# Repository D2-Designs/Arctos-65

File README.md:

# Arctos-65
Arctos 65 is a HHKB style 65% keyboard with a rotary encoder

Hello! This page is currently under construction. 

I plan to relase Version 1 of the project soon, which should fix all the issues with my innitial prototype, have more supported layouts, and be easier to manufacture.

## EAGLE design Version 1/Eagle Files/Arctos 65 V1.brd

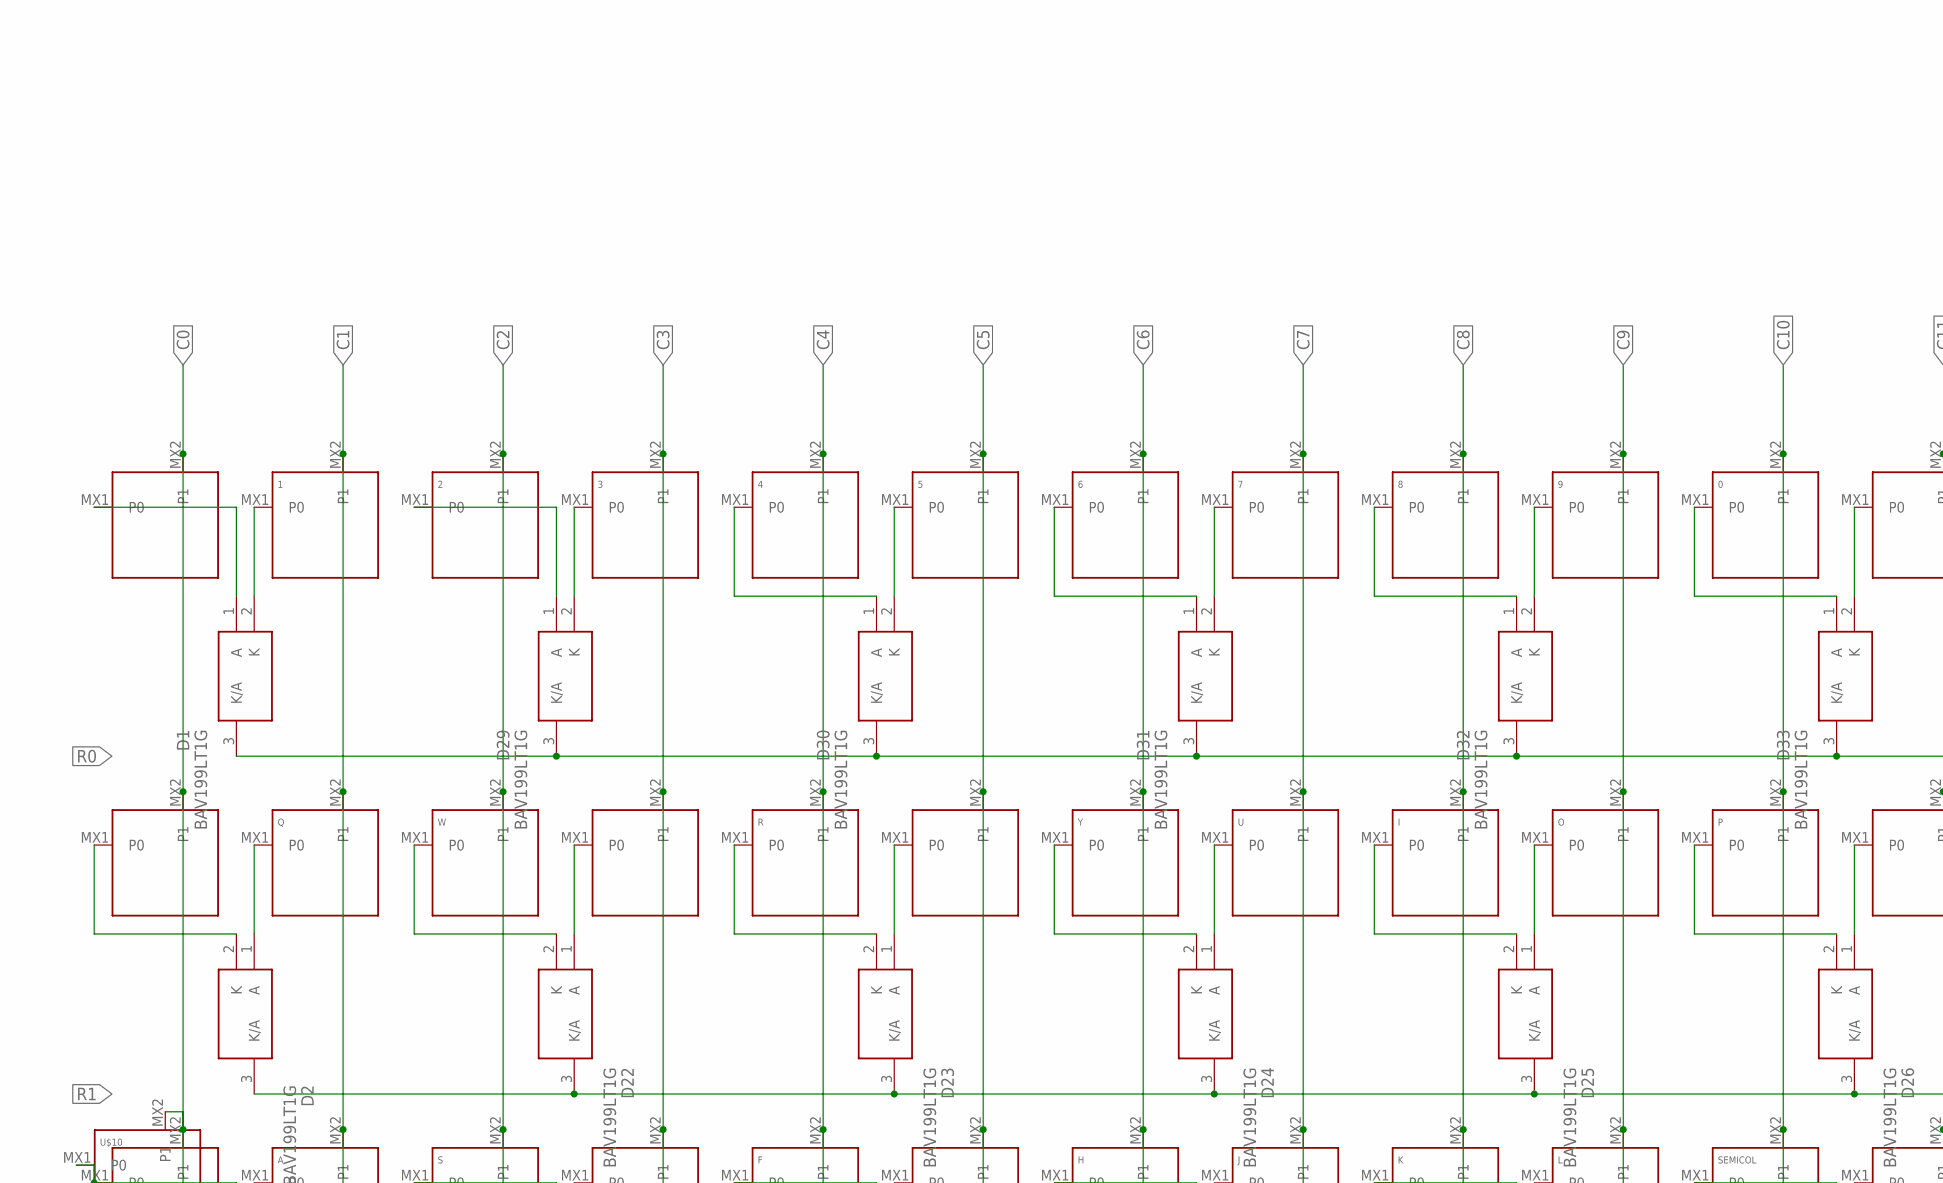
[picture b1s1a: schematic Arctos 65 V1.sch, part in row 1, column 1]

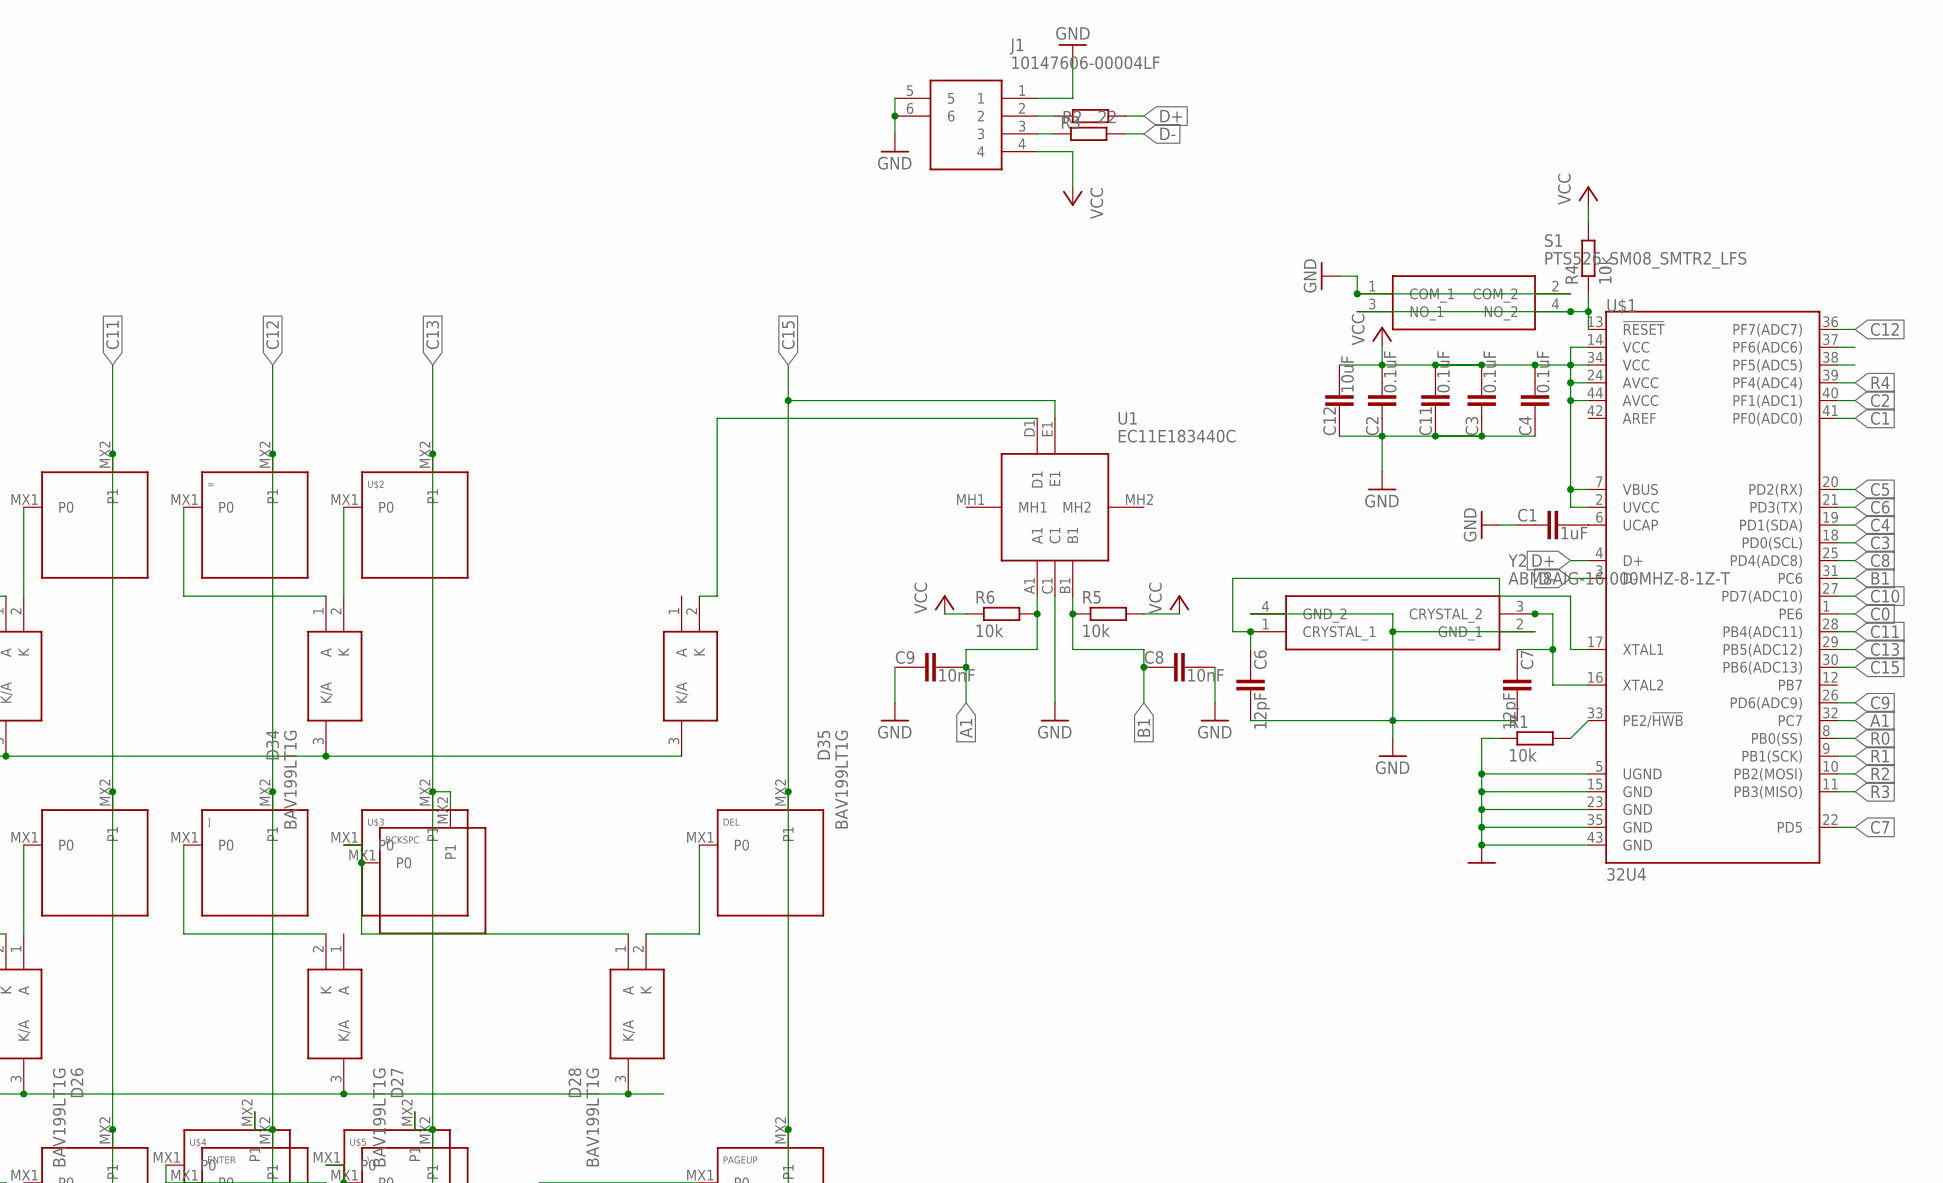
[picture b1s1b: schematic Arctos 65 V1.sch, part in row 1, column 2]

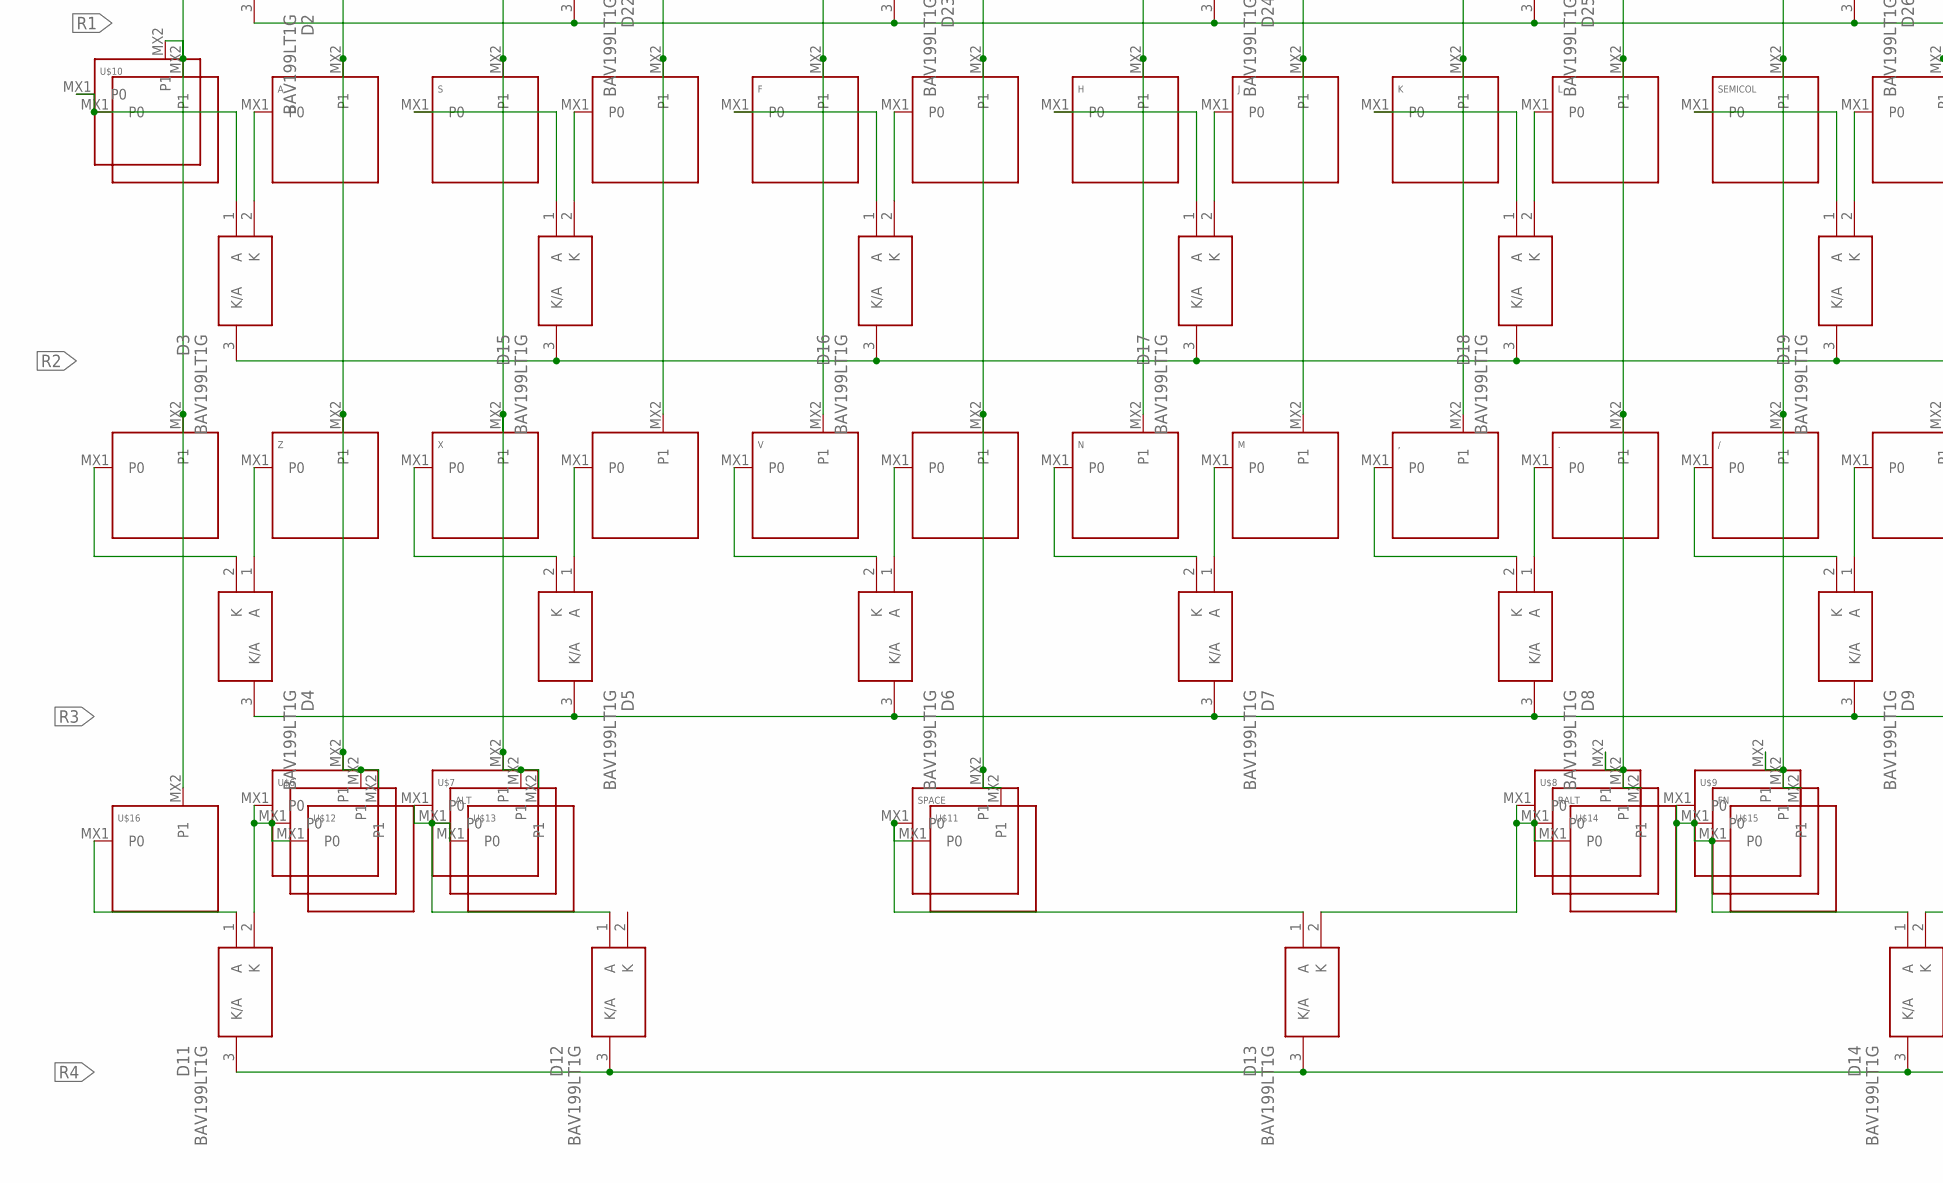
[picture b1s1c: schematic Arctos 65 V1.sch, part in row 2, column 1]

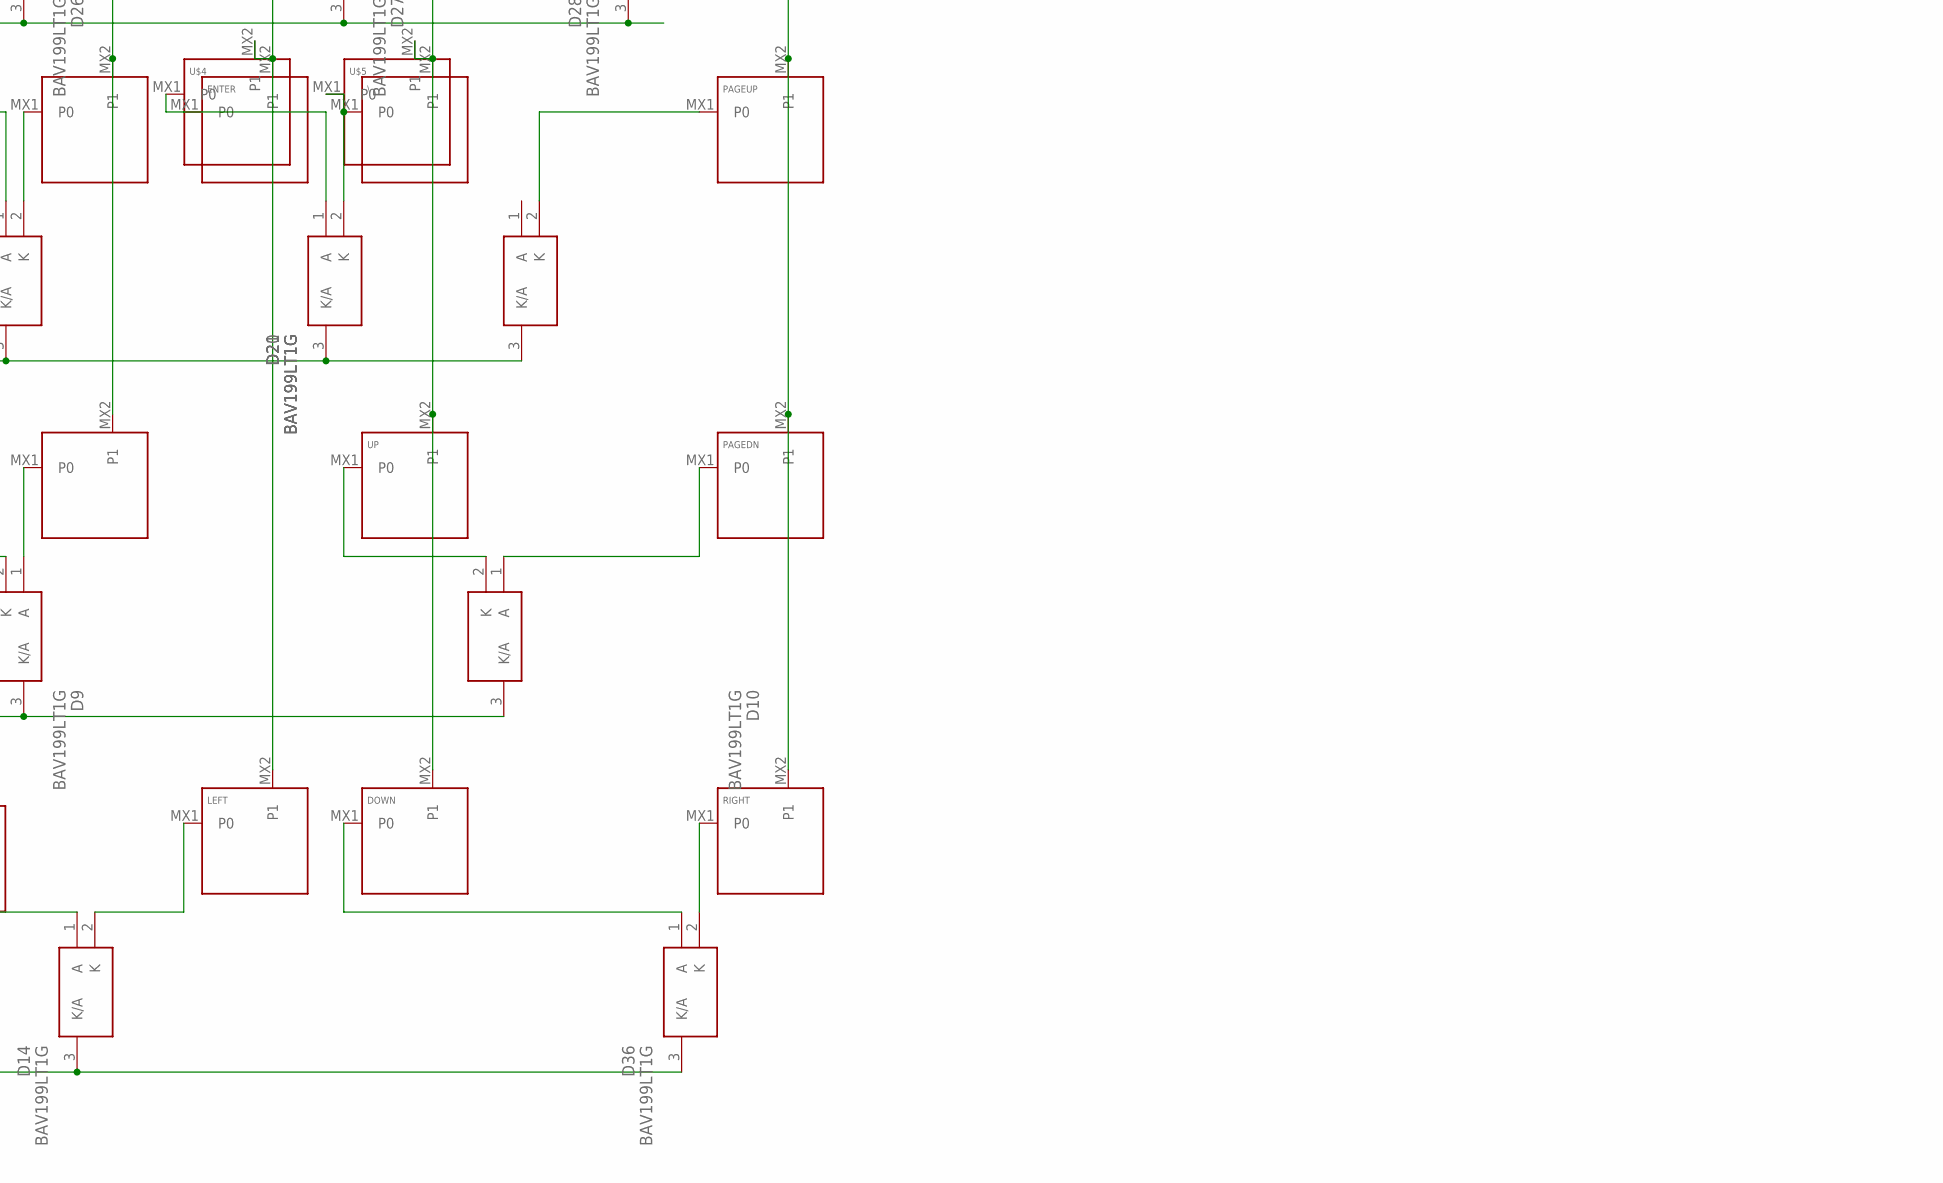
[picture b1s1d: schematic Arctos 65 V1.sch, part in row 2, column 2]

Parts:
0, 1, 2, 3, 4, 5, 6, 7, 8, 9, .: KEYSWITCH-PLAIN-MX-1U; MX-1U
': KEYSWITCH-PLAIN-MX-1U; MX-1U
,: KEYSWITCH-PLAIN-MX-1U; MX-1U
-: KEYSWITCH-PLAIN-MX-1U; MX-1U
/: KEYSWITCH-PLAIN-MX-1U; MX-1U
=: KEYSWITCH-PLAIN-MX-1U; MX-1U
A: KEYSWITCH-PLAIN-MX-1U; MX-1U
ALT: KEYSWITCH-PLAIN-MX-1U; MX-1U
B: KEYSWITCH-PLAIN-MX-1U; MX-1U
BCKSPC: KEYSWITCH-PLAIN-MX-2U; MX-2U
C: KEYSWITCH-PLAIN-MX-1U; MX-1U
C1: 1uF; C0603
C2, C3, C4, C11: 0.1uF; C0603
C6, C7: 12pF; C0603
C8, C9: 10nF; C0603
C12: 10uF; C0603
CAPS: KEYSWITCH-PLAIN-MX-1U; MX-1U
D: KEYSWITCH-PLAIN-MX-1U; MX-1U
D1, D2, D3, D4, D5, D6, D7, D8, D9, D10, D11, D12, D13, D14, D15, D16, D17, D18, D19, D20, D21, D22, D23, D24, D25, D26, D27, D28, D29, D30, D31, D32, D33, D34, D35, D36: BAV199LT1G; SOT96P237X111-3N
DEL: KEYSWITCH-PLAIN-MX-1U; MX-1U
DOWN: KEYSWITCH-PLAIN-MX-1U; MX-1U
E: KEYSWITCH-PLAIN-MX-1U; MX-1U
ENTER: KEYSWITCH-PLAIN-MX-2U; MX-2U
ESC: KEYSWITCH-PLAIN-MX-1U; MX-1U
F: KEYSWITCH-PLAIN-MX-1U; MX-1U
FN: KEYSWITCH-PLAIN-MX-1U; MX-1U
G: KEYSWITCH-PLAIN-MX-1U; MX-1U
H: KEYSWITCH-PLAIN-MX-1U; MX-1U
I: KEYSWITCH-PLAIN-MX-1U; MX-1U
J: KEYSWITCH-PLAIN-MX-1U; MX-1U
J1: 10147606-00004LF; 1014760600004LF
K: KEYSWITCH-PLAIN-MX-1U; MX-1U
L: KEYSWITCH-PLAIN-MX-1U; MX-1U
LEFT: KEYSWITCH-PLAIN-MX-1U; MX-1U
M: KEYSWITCH-PLAIN-MX-1U; MX-1U
N: KEYSWITCH-PLAIN-MX-1U; MX-1U
O: KEYSWITCH-PLAIN-MX-1U; MX-1U
P: KEYSWITCH-PLAIN-MX-1U; MX-1U
PAGEDN: KEYSWITCH-PLAIN-MX-1U; MX-1U
PAGEUP: KEYSWITCH-PLAIN-MX-1U; MX-1U
Q: KEYSWITCH-PLAIN-MX-1U; MX-1U
R: KEYSWITCH-PLAIN-MX-1U; MX-1U
R1, R4, R5, R6: 10k; R0603
R2, R3: 22; R0603
RALT: KEYSWITCH-PLAIN-MX-1U; MX-1U
RIGHT: KEYSWITCH-PLAIN-MX-1U; MX-1U
RSHIFT: KEYSWITCH-PLAIN-MX-1U; MX-1U
S: KEYSWITCH-PLAIN-MX-1U; MX-1U
S1: PTS526_SM08_SMTR2_LFS; PTS526SM08SMTR2LFS
SEMICOL: KEYSWITCH-PLAIN-MX-1U; MX-1U
SHIFT: KEYSWITCH-PLAIN-MX-2U; MX-2U
SPACE: KEYSWITCH-PLAIN-MX-7U-FLIPPED; MX-7U-FLIPPED
T: KEYSWITCH-PLAIN-MX-1U; MX-1U
TAB: KEYSWITCH-PLAIN-MX-1U; MX-1U
U: KEYSWITCH-PLAIN-MX-1U; MX-1U
U1: EC11E183440C
U$1: 32U4; TQFP44
U$2, U$3, U$4, U$6, U$7, U$8, U$9, U$10, U$12, U$13, U$14, U$15, U$16: KEYSWITCH-PLAIN-MX-1U; MX-1U
U$5: KEYSWITCH-PLAIN-MX-2U-ROTATED; MX-2U-ROTATED
U$11: KEYSWITCH-PLAIN-MX-6.25U-FLIPPED; MX-6.25U-FLIPPED
UP: KEYSWITCH-PLAIN-MX-1U; MX-1U
V: KEYSWITCH-PLAIN-MX-1U; MX-1U
W: KEYSWITCH-PLAIN-MX-1U; MX-1U
WIN: KEYSWITCH-PLAIN-MX-1U; MX-1U
X: KEYSWITCH-PLAIN-MX-1U; MX-1U
Y: KEYSWITCH-PLAIN-MX-1U; MX-1U
Y2: ABM8AIG-16.000MHZ-8-1Z-T; ABM8AIG16000MHZ81ZT
Z: KEYSWITCH-PLAIN-MX-1U; MX-1U
[: KEYSWITCH-PLAIN-MX-1U; MX-1U
\: KEYSWITCH-PLAIN-MX-1U; MX-1U
]: KEYSWITCH-PLAIN-MX-1U; MX-1U

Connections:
A1: C9.2, R6.2, U1.A1, U$1.32 (PC7)
B1: C8.1, R5.1, U1.B1, U$1.31 (PC6)
C0: CAPS.MX2 (P1), ESC.MX2 (P1), SHIFT.MX2 (P1), TAB.MX2 (P1), U$1.1 (PE6), U$10.MX2 (P1), U$16.MX2 (P1)
C1: 1.MX2 (P1), A.MX2 (P1), Q.MX2 (P1), U$1.41 (PF0(ADC0)), U$6.MX2 (P1), U$12.MX2 (P1), WIN.MX2 (P1), Z.MX2 (P1)
C2: 2.MX2 (P1), ALT.MX2 (P1), S.MX2 (P1), U$1.40 (PF1(ADC1)), U$7.MX2 (P1), U$13.MX2 (P1), W.MX2 (P1), X.MX2 (P1)
C3: 3.MX2 (P1), C.MX2 (P1), D.MX2 (P1), E.MX2 (P1), U$1.18 (PD0(SCL))
C4: 4.MX2 (P1), F.MX2 (P1), R.MX2 (P1), U$1.19 (PD1(SDA)), V.MX2 (P1)
C5: 5.MX2 (P1), B.MX2 (P1), G.MX2 (P1), SPACE.MX2 (P1), T.MX2 (P1), U$1.20 (PD2(RX)), U$11.MX2 (P1)
C6: 6.MX2 (P1), H.MX2 (P1), N.MX2 (P1), U$1.21 (PD3(TX)), Y.MX2 (P1)
C7: 7.MX2 (P1), J.MX2 (P1), M.MX2 (P1), U.MX2 (P1), U$1.22 (PD5)
C8: 8.MX2 (P1), ,.MX2 (P1), I.MX2 (P1), K.MX2 (P1), U$1.25 (PD4(ADC8))
C9: 9.MX2 (P1), ..MX2 (P1), L.MX2 (P1), O.MX2 (P1), RALT.MX2 (P1), U$1.26 (PD6(ADC9)), U$8.MX2 (P1), U$14.MX2 (P1)
C10: 0.MX2 (P1), /.MX2 (P1), FN.MX2 (P1), P.MX2 (P1), SEMICOL.MX2 (P1), U$1.27 (PD7(ADC10)), U$9.MX2 (P1), U$15.MX2 (P1)
C11: '.MX2 (P1), -.MX2 (P1), RSHIFT.MX2 (P1), U$1.28 (PB4(ADC11)), [.MX2 (P1)
C12: =.MX2 (P1), ENTER.MX2 (P1), LEFT.MX2 (P1), U$1.36 (PF7(ADC7)), U$4.MX2 (P1), ].MX2 (P1)
C13: BCKSPC.MX2 (P1), DOWN.MX2 (P1), U$1.29 (PB5(ADC12)), U$2.MX2 (P1), U$3.MX2 (P1), U$5.MX2 (P1), UP.MX2 (P1), \.MX2 (P1)
C15: DEL.MX2 (P1), PAGEDN.MX2 (P1), PAGEUP.MX2 (P1), RIGHT.MX2 (P1), U1.E1, U$1.30 (PB6(ADC13))
D+: R3.2, U$1.4 (D+)
D-: R2.2, U$1.3 (D-)
GND: C1.1, C2.1, C3.1, C4.1, C6.2, C7.2, C8.2, C9.1, C11.1, C12.1, J1.1, J1.5, J1.6, R1.1, S1.1 (COM_1), S1.2 (COM_2), U1.C1, U$1.5 (UGND), U$1.15 (GND), U$1.23 (GND), U$1.35 (GND), U$1.43 (GND), Y2.2 (GND_1), Y2.4 (GND_2)
unnamed: D28.2 (K), DEL.MX1 (P0)
unnamed: A.MX1 (P0), D3.2 (K)
unnamed: D20.1 (A), ENTER.MX1 (P0), U$4.MX1 (P0)
unnamed: D11.2 (K), U$6.MX1 (P0), U$12.MX1 (P0), WIN.MX1 (P0)
unnamed: ALT.MX1 (P0), D12.1 (A), U$7.MX1 (P0), U$13.MX1 (P0)
unnamed: D13.2 (K), RALT.MX1 (P0), U$8.MX1 (P0), U$14.MX1 (P0)
unnamed: D14.1 (A), FN.MX1 (P0), U$9.MX1 (P0), U$15.MX1 (P0)
unnamed: D11.1 (A), U$16.MX1 (P0)
unnamed: D1.1 (A), ESC.MX1 (P0)
unnamed: 1.MX1 (P0), D1.2 (K)
unnamed: D2.2 (K), TAB.MX1 (P0)
unnamed: D2.1 (A), Q.MX1 (P0)
unnamed: 2.MX1 (P0), D29.1 (A)
unnamed: 3.MX1 (P0), D29.2 (K)
unnamed: 4.MX1 (P0), D30.1 (A)
unnamed: 5.MX1 (P0), D30.2 (K)
unnamed: 6.MX1 (P0), D31.1 (A)
unnamed: 7.MX1 (P0), D31.2 (K)
unnamed: 8.MX1 (P0), D32.1 (A)
unnamed: 9.MX1 (P0), D32.2 (K)
unnamed: 0.MX1 (P0), D33.1 (A)
unnamed: -.MX1 (P0), D33.2 (K)
unnamed: =.MX1 (P0), D34.1 (A)
unnamed: D34.2 (K), U$2.MX1 (P0)
unnamed: D22.2 (K), W.MX1 (P0)
unnamed: D22.1 (A), E.MX1 (P0)
unnamed: D23.2 (K), R.MX1 (P0)
unnamed: D23.1 (A), T.MX1 (P0)
unnamed: D24.2 (K), Y.MX1 (P0)
unnamed: D24.1 (A), U.MX1 (P0)
unnamed: D25.2 (K), I.MX1 (P0)
unnamed: D25.1 (A), O.MX1 (P0)
unnamed: D26.2 (K), P.MX1 (P0)
unnamed: D26.1 (A), [.MX1 (P0)
unnamed: D27.2 (K), ].MX1 (P0)
unnamed: D15.1 (A), S.MX1 (P0)
unnamed: D35.2 (K), U1.D1
unnamed: D.MX1 (P0), D15.2 (K)
unnamed: D16.1 (A), F.MX1 (P0)
unnamed: CAPS.MX1 (P0), D3.1 (A), U$10.MX1 (P0)
unnamed: D16.2 (K), G.MX1 (P0)
unnamed: D17.1 (A), H.MX1 (P0)
unnamed: D17.2 (K), J.MX1 (P0)
unnamed: D18.1 (A), K.MX1 (P0)
unnamed: D18.2 (K), L.MX1 (P0)
unnamed: D19.1 (A), SEMICOL.MX1 (P0)
unnamed: '.MX1 (P0), D19.2 (K)
unnamed: D20.2 (K), U$5.MX1 (P0), \.MX1 (P0)
unnamed: D4.2 (K), SHIFT.MX1 (P0)
unnamed: D4.1 (A), Z.MX1 (P0)
unnamed: D5.2 (K), X.MX1 (P0)
unnamed: C.MX1 (P0), D5.1 (A)
unnamed: D6.2 (K), V.MX1 (P0)
unnamed: B.MX1 (P0), D6.1 (A)
unnamed: D7.2 (K), N.MX1 (P0)
unnamed: D7.1 (A), M.MX1 (P0)
unnamed: ,.MX1 (P0), D8.2 (K)
unnamed: ..MX1 (P0), D8.1 (A)
unnamed: /.MX1 (P0), D9.2 (K)
unnamed: D9.1 (A), RSHIFT.MX1 (P0)
unnamed: D10.2 (K), UP.MX1 (P0)
unnamed: J1.2, R3.1
unnamed: R1.2, U$1.33 (PE2/!HWB)
unnamed: J1.3, R2.1
unnamed: C1.2, U$1.6 (UCAP)
unnamed: C6.1, U$1.17 (XTAL1), Y2.1 (CRYSTAL_1)
unnamed: BCKSPC.MX1 (P0), D28.1 (A), U$3.MX1 (P0)
unnamed: D21.2 (K), PAGEUP.MX1 (P0)
unnamed: D10.1 (A), PAGEDN.MX1 (P0)
unnamed: D13.1 (A), SPACE.MX1 (P0), U$11.MX1 (P0)
unnamed: D14.2 (K), LEFT.MX1 (P0)
unnamed: D36.1 (A), DOWN.MX1 (P0)
unnamed: D36.2 (K), RIGHT.MX1 (P0)
unnamed: C7.1, U$1.16 (XTAL2), Y2.3 (CRYSTAL_2)
unnamed: R4.1, S1.3 (NO_1), S1.4 (NO_2), U$1.13 (!RESET)
R0: D1.3 (K/A), D29.3 (K/A), D30.3 (K/A), D31.3 (K/A), D32.3 (K/A), D33.3 (K/A), D34.3 (K/A), D35.3 (K/A), U$1.8 (PB0(SS))
R1: D2.3 (K/A), D22.3 (K/A), D23.3 (K/A), D24.3 (K/A), D25.3 (K/A), D26.3 (K/A), D27.3 (K/A), D28.3 (K/A), U$1.9 (PB1(SCK))
R2: D3.3 (K/A), D15.3 (K/A), D16.3 (K/A), D17.3 (K/A), D18.3 (K/A), D19.3 (K/A), D20.3 (K/A), D21.3 (K/A), U$1.10 (PB2(MOSI))
R3: D4.3 (K/A), D5.3 (K/A), D6.3 (K/A), D7.3 (K/A), D8.3 (K/A), D9.3 (K/A), D10.3 (K/A), U$1.11 (PB3(MISO))
R4: D11.3 (K/A), D12.3 (K/A), D13.3 (K/A), D14.3 (K/A), D36.3 (K/A), U$1.39 (PF4(ADC4))
VCC: C2.2, C3.2, C4.2, C11.2, C12.2, J1.4, R4.2, R5.2, R6.1, U$1.2 (UVCC), U$1.7 (VBUS), U$1.14 (VCC), U$1.24 (AVCC), U$1.34 (VCC), U$1.44 (AVCC)

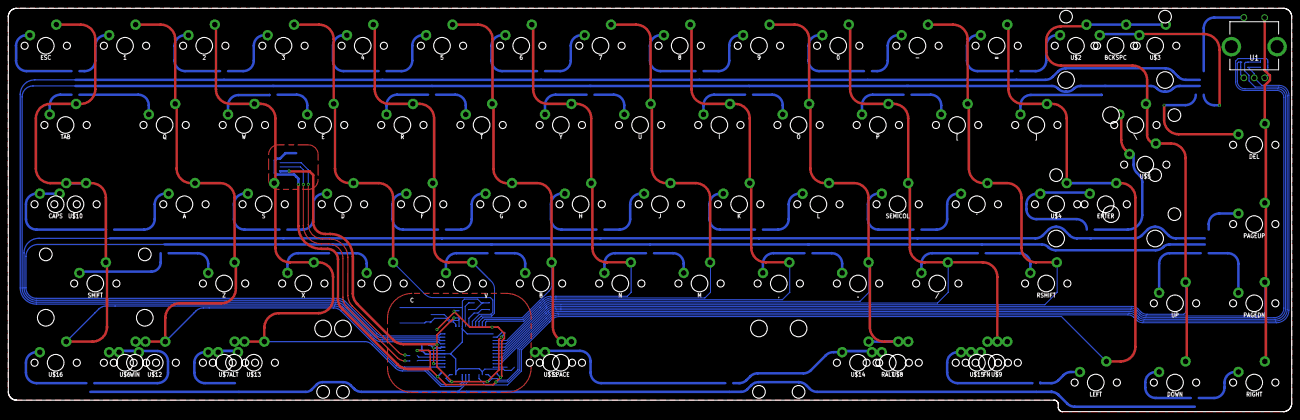
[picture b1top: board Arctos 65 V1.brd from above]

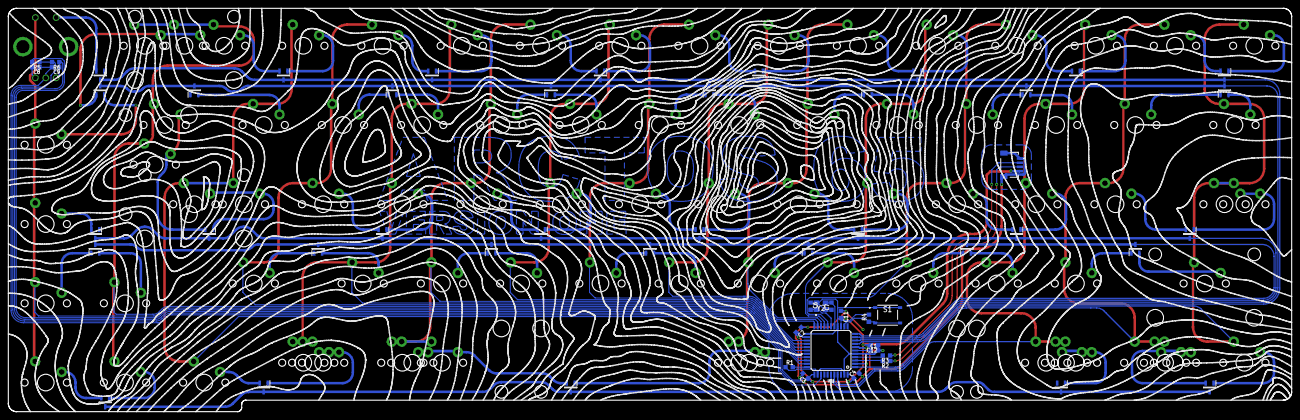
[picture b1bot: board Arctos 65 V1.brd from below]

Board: 2 copper layers, 308.5 x 97.0 mm, 137 parts (56 on the bottom side), 101 nets.

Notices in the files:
parts and their libraries:
SparkFun-IC-Microcontroller: Licensing: Creative Commons ShareAlike 4.0 International - https://creativecommons.org/licenses/by-sa/4.0
